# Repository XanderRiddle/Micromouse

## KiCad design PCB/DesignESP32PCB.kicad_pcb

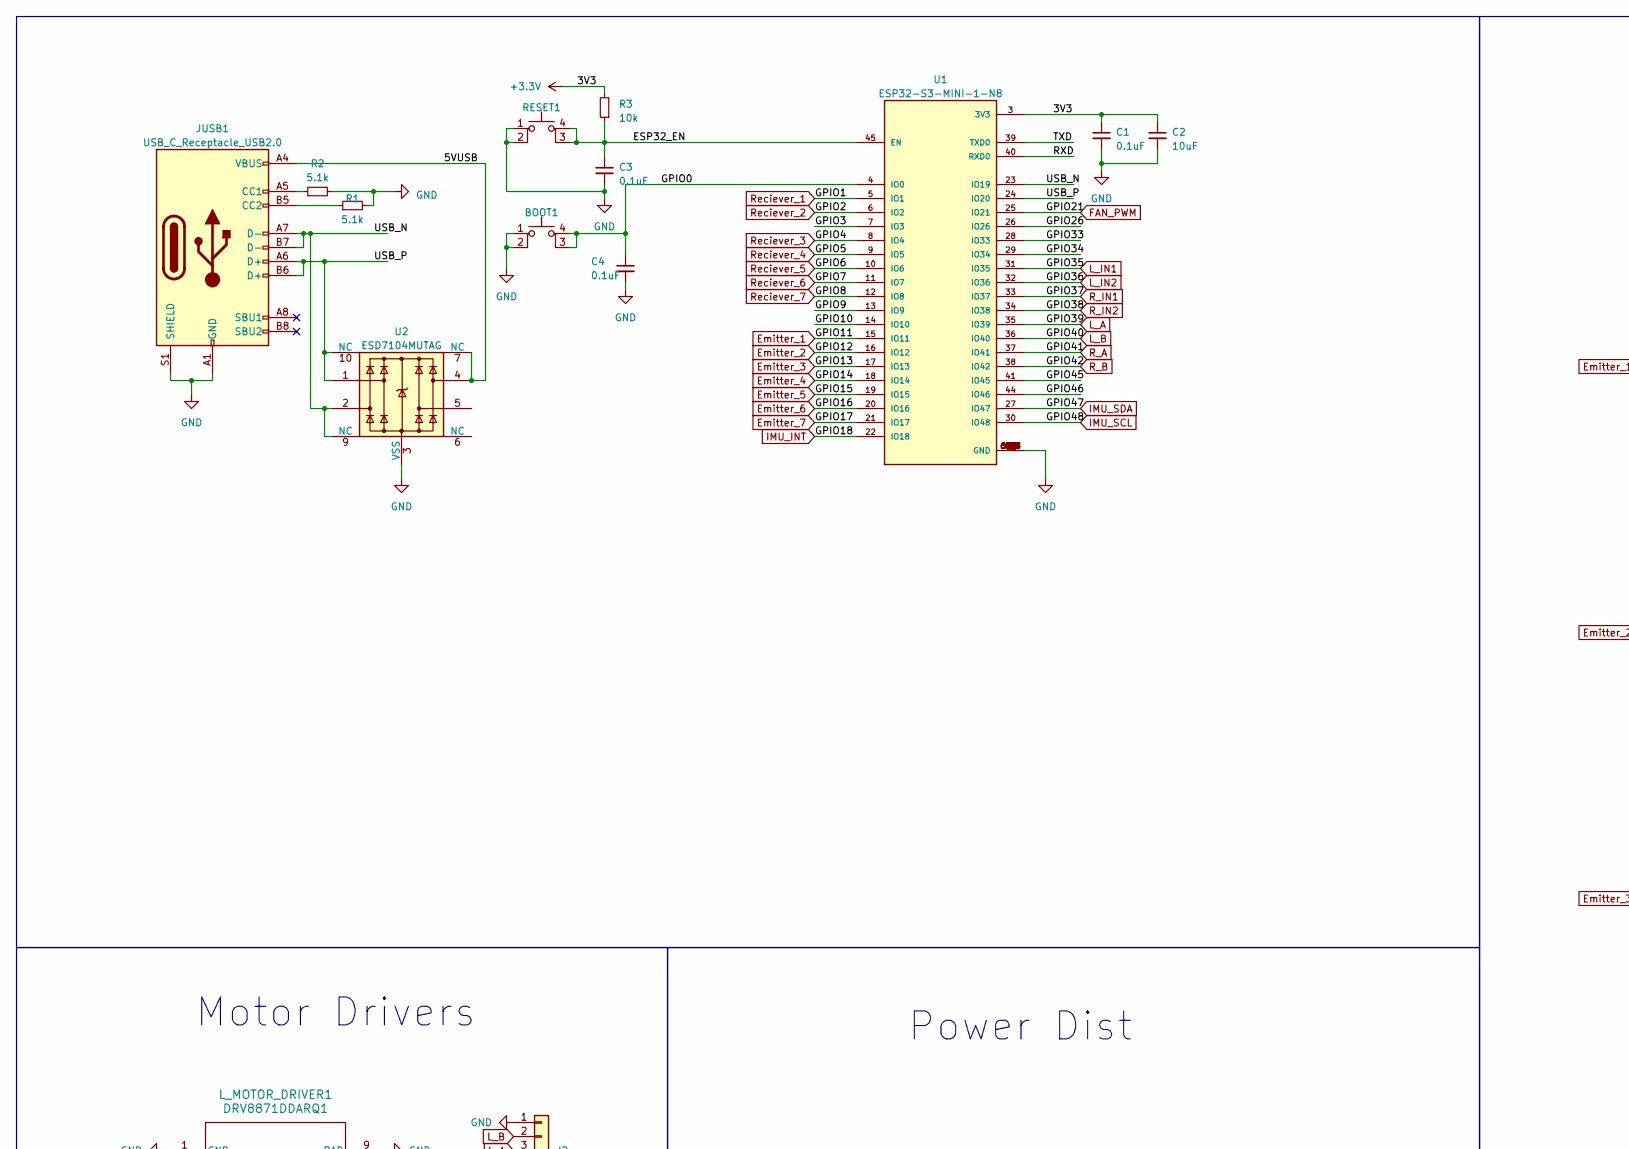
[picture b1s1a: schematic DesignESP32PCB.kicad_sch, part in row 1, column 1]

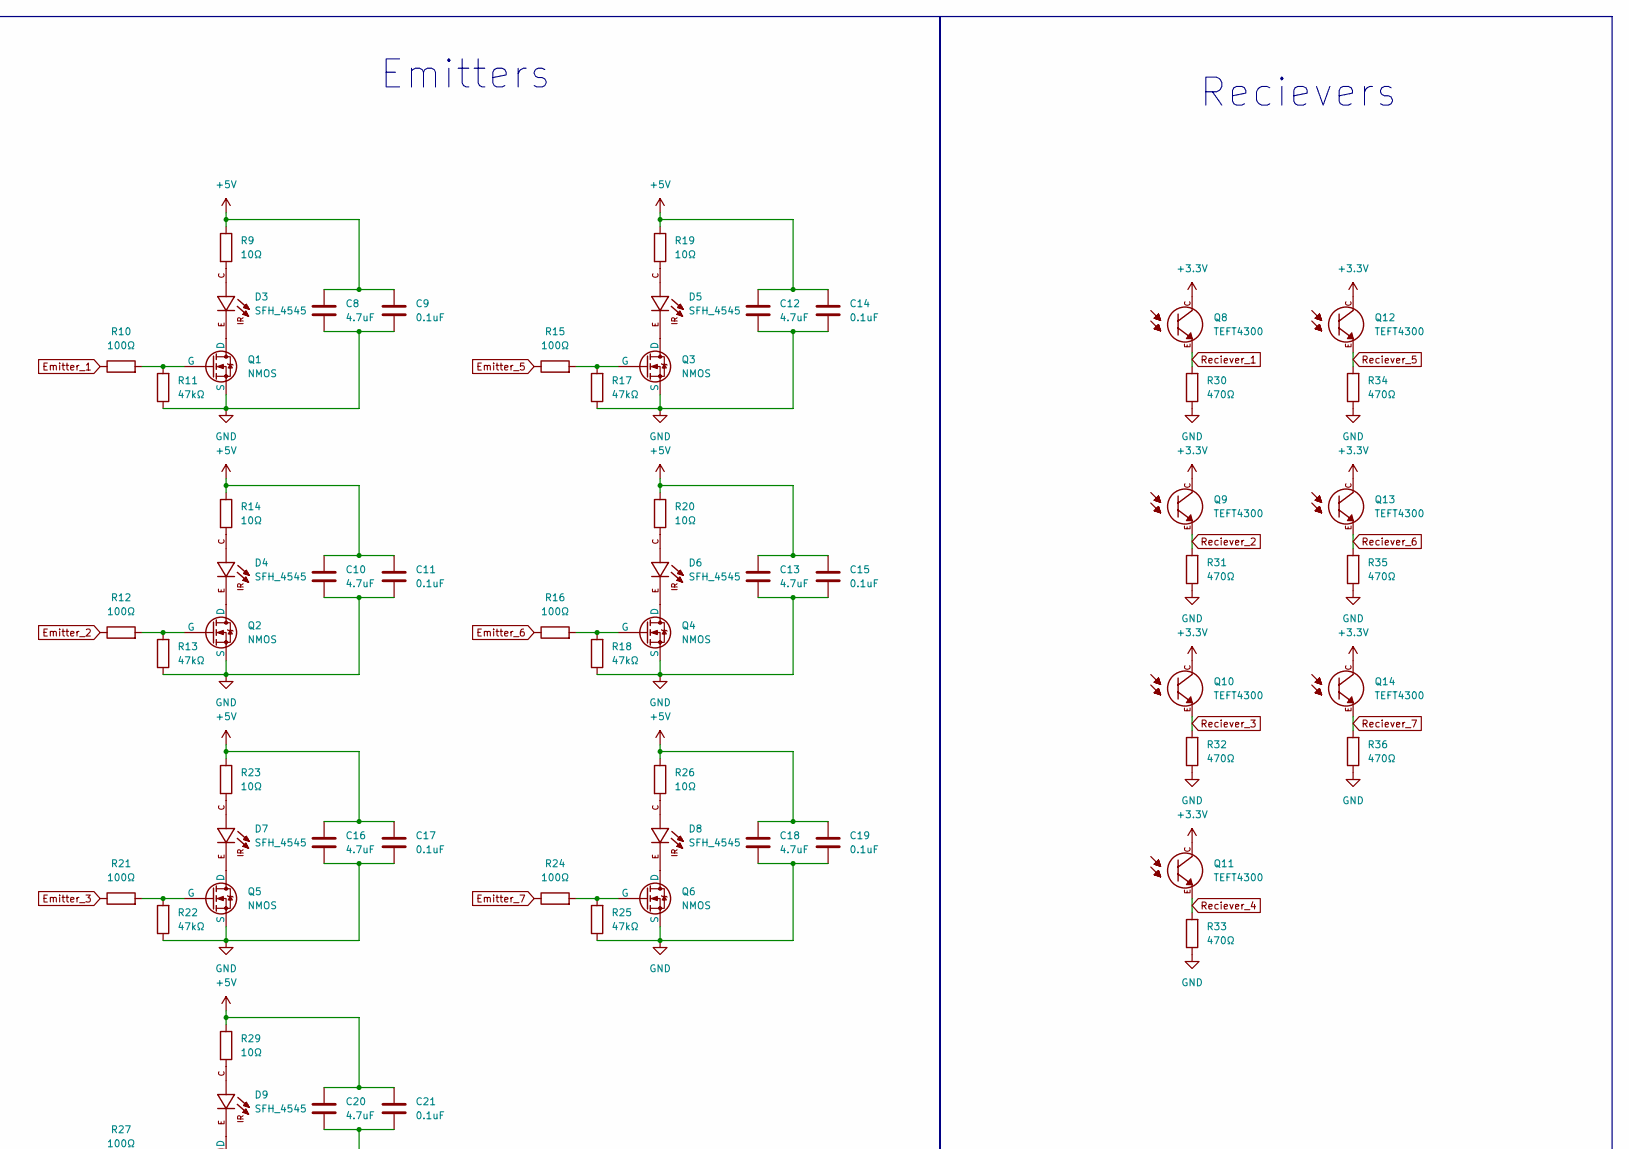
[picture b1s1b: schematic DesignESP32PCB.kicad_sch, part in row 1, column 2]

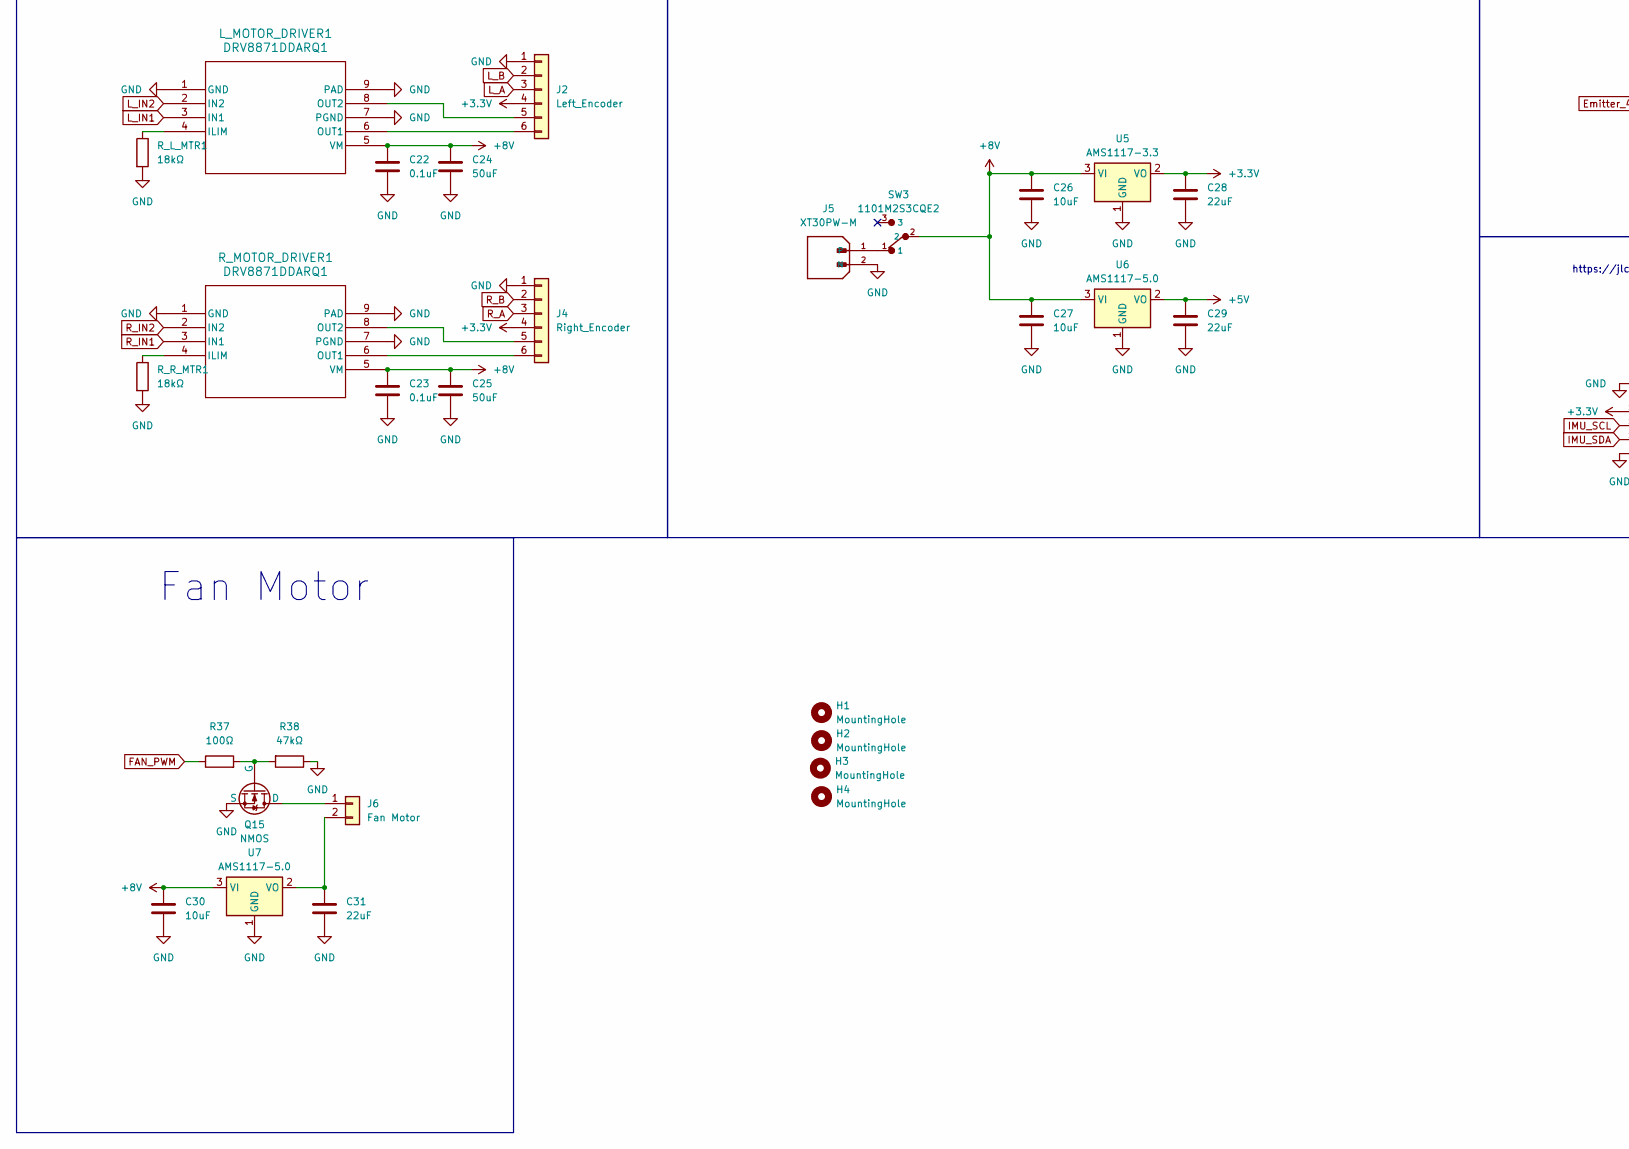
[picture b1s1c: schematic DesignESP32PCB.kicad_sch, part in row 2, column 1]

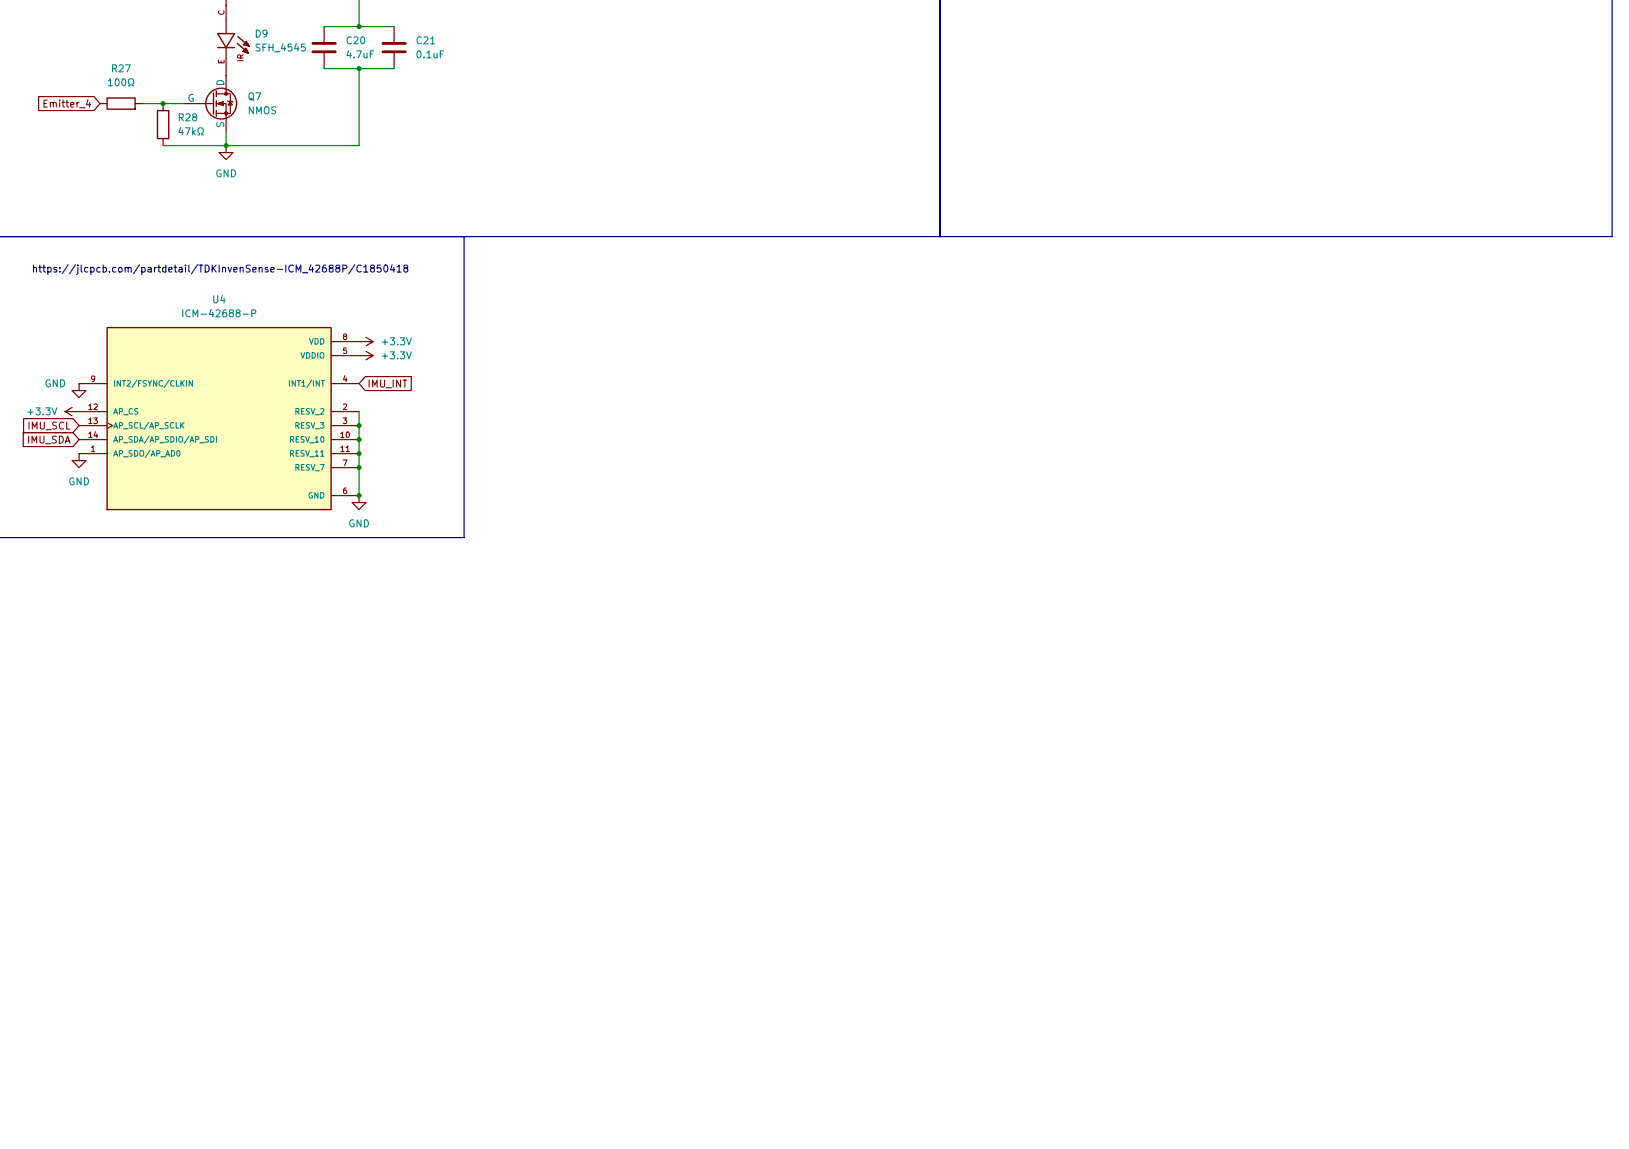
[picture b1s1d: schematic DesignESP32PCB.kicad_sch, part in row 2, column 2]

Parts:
BOOT1: SW_SPST_PTS810
C1, C3, C4, C9, C11, C14, C15, C17, C19, C21, C22, C23: 0.1uF; C_0603_1608Metric
C2, C26, C27, C30: 10uF; C_0603_1608Metric
C8, C10, C12, C13, C16, C18, C20: 4.7uF; C_0603_1608Metric
C24, C25: 50uF; C_0603_1608Metric
C28, C29, C31: 22uF; C_0603_1608Metric
D3, D4, D5, D6, D7, D8, D9: SFH_4545; XDCR_TEFT4300; PARTREV 1.5; DigiKey_Part_Number 475-SFH4545-ND
H1, H2, H3, H4: MountingHole; MountingHole_2.5mm
J2: Left_Encoder; JST_SH_BM06B-SRSS-TB_1x06-1MP_P1.00mm_Vertical
J4: Right_Encoder; JST_SH_BM06B-SRSS-TB_1x06-1MP_P1.00mm_Vertical
J5: XT30PW-M; JST_SH_BM02B-SRSS-TB_1x02-1MP_P1.00mm_Vertical; PARTREV 1.2
J6: Fan Motor; JST_SH_BM02B-SRSS-TB_1x02-1MP_P1.00mm_Vertical
JUSB1: USB_C_Receptacle_USB2.0; USB_C_Receptacle_GCT_USB4105-xx-A_16P_TopMnt_Horizontal
L_MOTOR_DRIVER1: DRV8871DDARQ1; DDA0008H_N_TEX
Q1, Q2, Q3, Q4, Q5, Q6, Q7, Q15: NMOS; SOT95P280X125-3N
Q8, Q9, Q10, Q11, Q12, Q13, Q14: TEFT4300; XDCR_TEFT4300; DigiKey_Part_Number 751-1041-ND
R1, R2: 5.1k; R_0603_1608Metric
R3: 10k; R_0603_1608Metric
R9, R14, R19, R20, R23, R26, R29: 10Ω; R_0603_1608Metric
R10, R12, R15, R16, R21, R24, R27, R37: 100Ω; R_0603_1608Metric
R11, R13, R17, R18, R22, R25, R28, R38: 47kΩ; R_0603_1608Metric
R30, R31, R32, R33, R34, R35, R36: 470Ω; R_0603_1608Metric
RESET1: SW_SPST_PTS810
R_L_MTR1: 18kΩ; R_0603_1608Metric
R_MOTOR_DRIVER1: DRV8871DDARQ1; DDA0008H_N_TEX
R_R_MTR1: 18kΩ; R_0603_1608Metric
SW3: 1101M2S3CQE2; SW_SPDT_CK_JS102011SAQN
U1: ESP32-S3-MINI-1-N8; XCVR_ESP32-S3-MINI-1-N8; PARTREV v0.6
U2: ESD7104MUTAG; Diodes_UDFN-10_1.0x2.5mm_P0.5mm
U4: ICM-42688-P; PQFN50P300X250X97-14N; PARTREV 1.2
U5: AMS1117-3.3; SOT-223-3_TabPin2
U6, U7: AMS1117-5.0; SOT-223-3_TabPin2

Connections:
+3.3V: C1.1, C2.1, C28.1, J2.4, J4.4, Q8.C, Q9.C, Q10.C, Q11.C, Q12.C, Q13.C, Q14.C, R3.2, U1.3 (3V3), U4.5 (VDDIO), U4.8 (VDD), U4.12 (AP_CS), U5.2 (VO)
+5V: C8.1, C9.1, C10.1, C11.1, C12.1, C13.1, C14.1, C15.1, C16.1, C17.1, C18.1, C19.1, C20.1, C21.1, C29.1, R9.1, R14.1, R19.1, R20.1, R23.1, R26.1, R29.1, U6.2 (VO)
+8V: C22.1, C23.1, C24.1, C25.1, C26.1, C27.1, C30.1, L_MOTOR_DRIVER1.5 (VM), R_MOTOR_DRIVER1.5 (VM), SW3.2, U5.3 (VI), U6.3 (VI), U7.3 (VI)
/5VUSB: JUSB1.A4 (VBUS), JUSB1.A9 (VBUS), JUSB1.B4 (VBUS), JUSB1.B9 (VBUS), U2.4, U2.7 (NC)
/ESP32_EN: C3.1, R3.1, RESET1.3 (K), RESET1.4 (A), U1.45 (EN)
/GPIO0: BOOT1.3 (K), BOOT1.4 (A), C4.1, U1.4 (IO0)
/GPIO3: U1.7 (IO3)
/GPIO9: U1.13 (IO9)
/GPIO10: U1.14 (IO10)
/GPIO26: U1.26 (IO26)
/GPIO33: U1.28 (IO33)
/GPIO34: U1.29 (IO34)
/GPIO45: U1.41 (IO45)
/GPIO46: U1.44 (IO46)
/RXD: U1.40 (RXD0)
/TXD: U1.39 (TXD0)
/USB_N: JUSB1.A7 (D-), JUSB1.B7 (D-), U1.23 (IO19), U2.2, U2.9 (NC)
/USB_P: JUSB1.A6 (D+), JUSB1.B6 (D+), U1.24 (IO20), U2.1, U2.10 (NC)
Emitter_1: R10.1, U1.15 (IO11)
Emitter_2: R12.1, U1.16 (IO12)
Emitter_3: R21.1, U1.17 (IO13)
Emitter_4: R27.1, U1.18 (IO14)
Emitter_5: R15.1, U1.19 (IO15)
Emitter_6: R16.1, U1.20 (IO16)
Emitter_7: R24.1, U1.21 (IO17)
FAN_PWM: R37.1, U1.25 (IO21)
GND: BOOT1.1, BOOT1.2, C1.2, C2.2, C3.2, C4.2, C8.2, C9.2, C10.2, C11.2, C12.2, C13.2, C14.2, C15.2, C16.2, C17.2, C18.2, C19.2, C20.2, C21.2, C22.2, C23.2, C24.2, C25.2, C26.2, C27.2, C28.2, C29.2, C30.2, C31.2, J2.1, J4.1, J5.2 (N), JUSB1.A1 (GND), JUSB1.A12 (GND), JUSB1.B1 (GND), JUSB1.B12 (GND), JUSB1.S1 (SHIELD), L_MOTOR_DRIVER1.1 (GND), L_MOTOR_DRIVER1.7 (PGND), L_MOTOR_DRIVER1.9 (PAD), Q1.3 (S), Q2.3 (S), Q3.3 (S), Q4.3 (S), Q5.3 (S), Q6.3 (S), Q7.3 (S), Q15.3 (S), R1.2, R2.2, R11.1, R13.1, R17.1, R18.1, R22.1, R25.1, R28.1, R30.1, R31.1, R32.1, R33.1, R34.1, R35.1, R36.1, R38.1, RESET1.1, RESET1.2, R_L_MTR1.2, R_MOTOR_DRIVER1.1 (GND), R_MOTOR_DRIVER1.7 (PGND), R_MOTOR_DRIVER1.9 (PAD), R_R_MTR1.2, U1.1 (GND), U1.2 (GND), U1.42 (GND), U1.43 (GND), U1.46 (GND), U1.47 (GND), U1.48 (GND), U1.49 (GND), U1.50 (GND), U1.51 (GND), U1.52 (GND), U1.53 (GND), U1.54 (GND), U1.55 (GND), U1.56 (GND), U1.57 (GND), U1.58 (GND), U1.59 (GND), U1.60 (GND), U1.61 (GND), U1.61_1 (GND), U1.61_2 (GND), U1.61_3 (GND), U1.61_4 (GND), U1.61_5 (GND), U1.61_6 (GND), U1.61_7 (GND), U1.61_8 (GND), U1.62 (GND), U1.63 (GND), U1.64 (GND), U1.65 (GND), U2.3 (VSS), U2.8 (VSS), U4.1 (AP_SDO/AP_AD0), U4.2 (RESV_2), U4.3 (RESV_3), U4.6 (GND), U4.7 (RESV_7), U4.9 (INT2/FSYNC/CLKIN), U4.10 (RESV_10), U4.11 (RESV_11), U5.1 (GND), U6.1 (GND), U7.1 (GND)
IMU_INT: U1.22 (IO18), U4.4 (INT1/INT)
IMU_SCL: U1.30 (IO48), U4.13 (AP_SCL/AP_SCLK)
IMU_SDA: U1.27 (IO47), U4.14 (AP_SDA/AP_SDIO/AP_SDI)
L_A: J2.3, U1.35 (IO39)
L_B: J2.2, U1.36 (IO40)
L_IN1: L_MOTOR_DRIVER1.3 (IN1), U1.31 (IO35)
L_IN2: L_MOTOR_DRIVER1.2 (IN2), U1.32 (IO36)
unnamed: D3.C, R9.2
unnamed: D4.C, R14.2
unnamed: D5.C, R19.2
unnamed: D6.C, R20.2
unnamed: D7.C, R23.2
unnamed: D8.C, R26.2
unnamed: D9.C, R29.2
unnamed: J2.5, L_MOTOR_DRIVER1.8 (OUT2)
unnamed: J2.6, L_MOTOR_DRIVER1.6 (OUT1)
unnamed: J4.5, R_MOTOR_DRIVER1.8 (OUT2)
unnamed: J4.6, R_MOTOR_DRIVER1.6 (OUT1)
unnamed: J5.1, SW3.1
unnamed: J6.1, Q15.1 (D)
unnamed: C31.1, J6.2, U7.2 (VO)
unnamed: JUSB1.A5 (CC1), R2.1
unnamed: JUSB1.B5 (CC2), R1.1
unnamed: L_MOTOR_DRIVER1.4 (ILIM), R_L_MTR1.1
unnamed: D3.E, Q1.1 (D)
unnamed: Q1.2 (G), R10.2, R11.2
unnamed: D4.E, Q2.1 (D)
unnamed: Q2.2 (G), R12.2, R13.2
unnamed: D5.E, Q3.1 (D)
unnamed: Q3.2 (G), R15.2, R17.2
unnamed: D6.E, Q4.1 (D)
unnamed: Q4.2 (G), R16.2, R18.2
unnamed: D7.E, Q5.1 (D)
unnamed: Q5.2 (G), R21.2, R22.2
unnamed: D8.E, Q6.1 (D)
unnamed: Q6.2 (G), R24.2, R25.2
unnamed: D9.E, Q7.1 (D)
unnamed: Q7.2 (G), R27.2, R28.2
unnamed: Q15.2 (G), R37.2, R38.2
unnamed: R_MOTOR_DRIVER1.4 (ILIM), R_R_MTR1.1
R_A: J4.3, U1.37 (IO41)
R_B: J4.2, U1.38 (IO42)
R_IN1: R_MOTOR_DRIVER1.3 (IN1), U1.33 (IO37)
R_IN2: R_MOTOR_DRIVER1.2 (IN2), U1.34 (IO38)
Reciever_1: Q8.E, R30.2, U1.5 (IO1)
Reciever_2: Q9.E, R31.2, U1.6 (IO2)
Reciever_3: Q10.E, R32.2, U1.8 (IO4)
Reciever_4: Q11.E, R33.2, U1.9 (IO5)
Reciever_5: Q12.E, R34.2, U1.10 (IO6)
Reciever_6: Q13.E, R35.2, U1.11 (IO7)
Reciever_7: Q14.E, R36.2, U1.12 (IO8)

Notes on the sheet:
Motor Drivers
https://jlcpcb.com/partdetail/TDKInvenSense-ICM_42688P/C1850418
Fan Motor
Emitters
Recievers
Power Dist

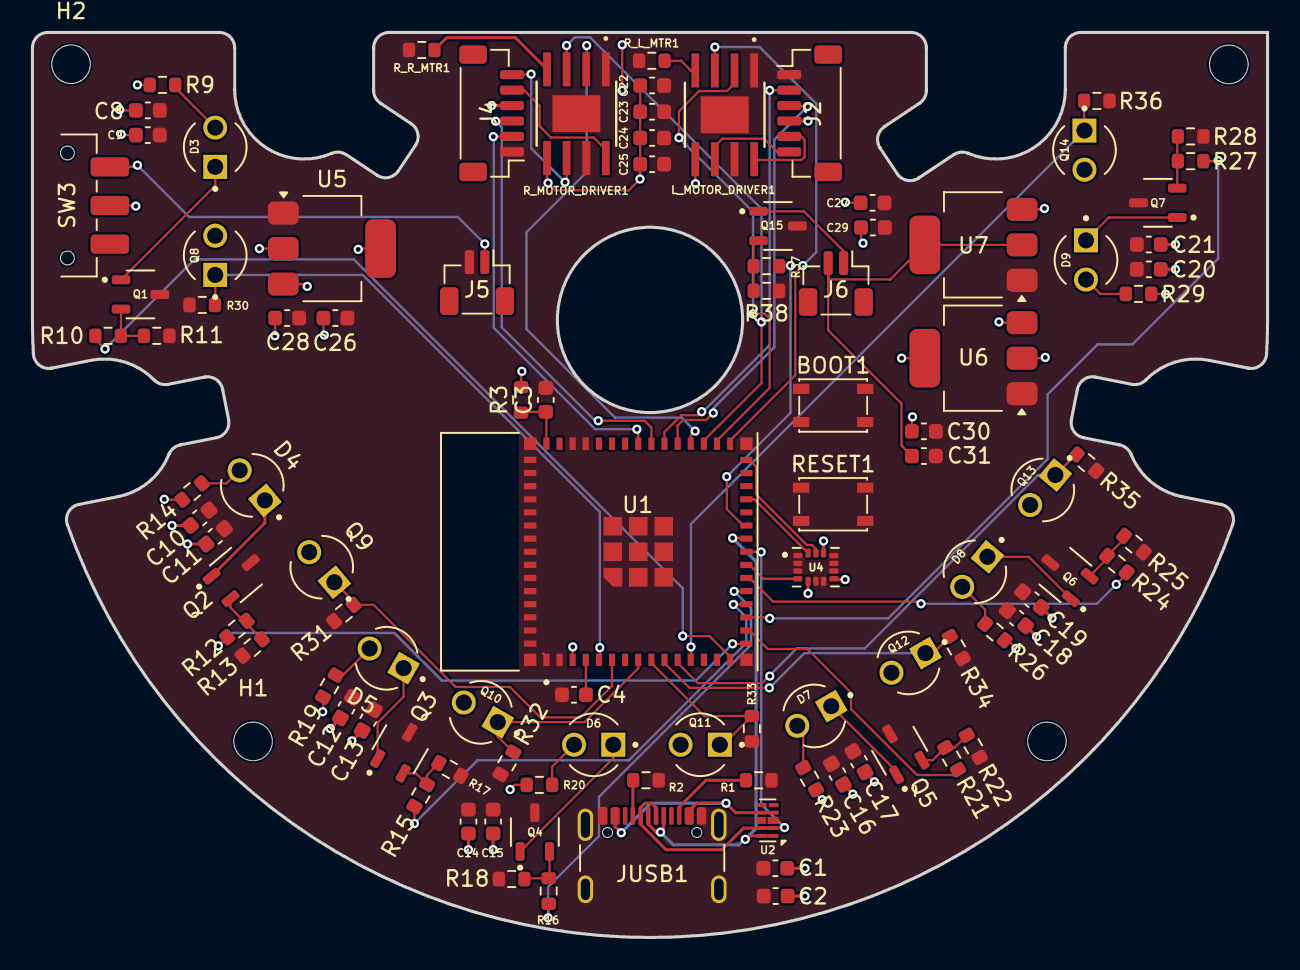
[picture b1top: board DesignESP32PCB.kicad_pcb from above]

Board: 4 copper layers, 80.0 x 58.6 mm, 105 parts (0 on the bottom side), 68 nets.
